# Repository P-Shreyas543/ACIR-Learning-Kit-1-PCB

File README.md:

# ACIR Learning Kits - Characterization & Experimentation Platform

**Decibels Lab Pvt Ltd**  
*Project Repository: [ACIR-Learning-Kit-1-PCB](https://github.com/P-Shreyas543/ACIR-Learning-Kit-1-PCB)*  
*Revision: v2.1 | Date: 2026-09-17*

---

## Overview

The **ACIR Learning Kits** are specialized, production-ready hardware characterization platforms designed for educational, research, and laboratory electrochemical impedance spectroscopy (EIS) and AC internal resistance (ACIR) testing of 18650 lithium-ion cells.

The repository contains two distinct learning kits:

### Learning Kit 1: Baseline Cell & Pack Topology Kit
1. **1S 1P Baseline Cell**: Single 18650 cell baseline ACIR characterization.
2. **1S 4P Parallel Pack**: Four-cell parallel module for current-sharing, contact resistance, and parallel cell mismatch studies.
3. **4S 1P Series String**: Four-cell series string for cumulative pack impedance and inter-cell busbar resistance.

### Learning Kit 2: Track Resistance & Interconnect Impedance Kit
1. **PCB Track Resistance Module**:
   - 3 calibrated test tracks with identical $6.0\text{ mm}$ width and varying lengths ($104.4\text{ mm}$, $58.0\text{ mm}$, $36.4\text{ mm}$).
   - Mirrored symmetrically on both copper layers (`F.Cu` and `B.Cu`).
   - Densely stitched with regular via matrices ($0.8\text{ mm}$ diameter, $0.4\text{ mm}$ drill).
   - Dedicated Kelvin test point probes: `P1` & `P2` (Track 1), `P3` & `P4` (Track 2), `P5` & `P6` (Track 3).
2. **4S 1P - (I) Module (Differential Cell ACIR Experiment)**:
   - 4 series cells (`BT2`, `BT3`, `BT4`, `BT5`) with uniform, ultra-low resistance interconnect buses ($8.0\text{ mm}$ 2-layer with dense via arrays).
   - Pack terminals: `B +ve` (BT2) and `B -ve` (BT5).
   - Students insert cells with *different* known ACIR values to observe that total pack ACIR is dominated by the sum of individual cell ACIRs when bus resistances are identical and negligible.
3. **4S 1P - (II) Module (Varying Interconnect Impedance Experiment)**:
   - 4 series cells (`BT6`, `BT7`, `BT8`, `BT9`) with deliberately *varying* interconnect track resistances:
     - **Link 1** (`BT6` $\leftrightarrow$ `BT7`): Ultra-wide $10.0\text{ mm}$ 2-layer bus with dense via matrix ($\approx 0.5\text{ m}\Omega$).
     - **Link 2** (`BT7` $\leftrightarrow$ `BT8`): Medium $3.0\text{ mm}$ single-layer trace ($\approx 3.0\text{ m}\Omega$).
     - **Link 3** (`BT8` $\leftrightarrow$ `BT9`): Narrow $0.8\text{ mm}$ single-layer trace ($\approx 10.0\text{ m}\Omega$).
   - Pack terminals: `B +ve` (BT6) and `B -ve` (BT9).
   - Students insert cells with *identical* ACIR values to demonstrate how interconnect trace impedance directly inflates total battery pack ACIR.

---

## Repository Structure

```
c:/Users/Shreyas/Documents/ACIR_PCB/
├── README.md                                  # Workspace Platform Documentation
├── .gitignore                                 # Git Ignore Configuration
├── ACIR-Learning-Kit-1-PCB/                   # Learning Kit 1 Project Directory
│   ├── ACIR-Learning-Kit-1-PCB.kicad_pro      # KiCad 10 Project File
│   ├── ACIR-Learning-Kit-1-PCB.kicad_pcb      # 2-Layer PCB Layout File
│   ├── ACIR-Learning-Kit-1-PCB.kicad_sch      # Complete Schematic Design
│   ├── ACIR-Learning-Kit-1-PCB.kicad_prl      # User Settings & Display Cache
│   ├── ACIR-Learning-Kit-1-PCB_BOM.csv        # Bill of Materials
│   ├── ACIR-Learning-Kit-1-PCB_LAYOUT.pdf     # Vector Layout Drawing
│   ├── ACIR-Learning-Kit-1-PCB_SCH.pdf        # Vector Schematic Drawing
│   ├── ACIR-Learning-Kit-1-PCB-drc.rpt        # DRC Verification Report (0 violations)
│   ├── ACIR-Learning-Kit-1-PCB-erc.rpt        # ERC Verification Report (0 errors)
│   ├── fp-lib-table                           # Footprint Library Table
│   ├── footprints.pretty/                     # Project Footprint Library
│   ├── gerbers/                               # RS-274X Gerbers & Drill Files
│   └── production/                            # JLCPCB Fabrication Deliverables
│       ├── ACIR-Learning-Kit-1-PCB_gerbers.zip# Complete Fabrication Archive
│       ├── ACIR-Learning-Kit-1-PCB_LAYOUT.pdf # Layout Drawing PDF
│       ├── ACIR-Learning-Kit-1-PCB_SCH.pdf    # Schematic Drawing PDF
│       ├── bom.csv                            # Component BOM
│       ├── positions.csv                      # Centroid Component Placement
│       └── netlist.ipc                        # IPC-D-356 Test Netlist
│
└── ACIR-Learning-Kit-2-PCB/                   # Learning Kit 2 Project Directory
    ├── ACIR-Learning-Kit-2-PCB.kicad_pro      # KiCad 10 Project File
    ├── ACIR-Learning-Kit-2-PCB.kicad_pcb      # 2-Layer PCB Layout File
    ├── ACIR-Learning-Kit-2-PCB.kicad_sch      # Complete Schematic Design
    ├── ACIR-Learning-Kit-2-PCB.kicad_prl      # User Settings & Display Cache
    ├── ACIR-Learning-Kit-2-PCB_BOM.csv        # Bill of Materials
    ├── ACIR-Learning-Kit-2-PCB_LAYOUT.pdf     # Vector Layout Drawing
    ├── ACIR-Learning-Kit-2-PCB_SCH.pdf        # Vector Schematic Drawing
    ├── ACIR-Learning-Kit-2-PCB-drc.rpt        # DRC Verification Report (0 violations)
    ├── ACIR-Learning-Kit-2-PCB-erc.rpt        # ERC Verification Report (0 errors)
    ├── kit2_render_top.png                    # Photorealistic 3D Top Render
    ├── kit2_render_bottom.png                 # Photorealistic 3D Bottom Render
    ├── fp-lib-table                           # Footprint Library Table
    ├── footprints.pretty/                     # Project Footprint Library
    ├── gerbers/                               # RS-274X Gerbers & Drill Files
    └── production/                            # JLCPCB Fabrication Deliverables
        ├── ACIR-Learning-Kit-2-PCB_gerbers.zip# Complete Fabrication Archive
        ├── ACIR-Learning-Kit-2-PCB_LAYOUT.pdf # Layout Drawing PDF
        ├── ACIR-Learning-Kit-2-PCB_SCH.pdf    # Schematic Drawing PDF
        ├── bom.csv                            # Component BOM
        ├── positions.csv                      # Centroid Component Placement
        └── netlist.ipc                        # IPC-D-356 Test Netlist
```

---

## PCB Specifications (Both Kits)

- **Dimensions**: $297.0\text{ mm} \times 210.0\text{ mm}$ (Standard A4 Landscape)
- **Layer Count**: 2 Layers ($1\text{ oz}$ / $35\,\mu\text{m}$ copper per layer)
- **Board Thickness**: $1.6\text{ mm}$ FR-4
- **Surface Finish**: HASL / ENIG compatible
- **Fabrication Compliance**: Verified 100% compliant with JLCPCB 2-layer fabrication capabilities:
  - **DRC**: **0 violations**, **0 unconnected pads**
  - **ERC**: **0 violations**, **0 errors**, **0 warnings**

---

## Design Team
- **Ashutosh Raj**
- **Shreyas P**
- **Suraj S D**

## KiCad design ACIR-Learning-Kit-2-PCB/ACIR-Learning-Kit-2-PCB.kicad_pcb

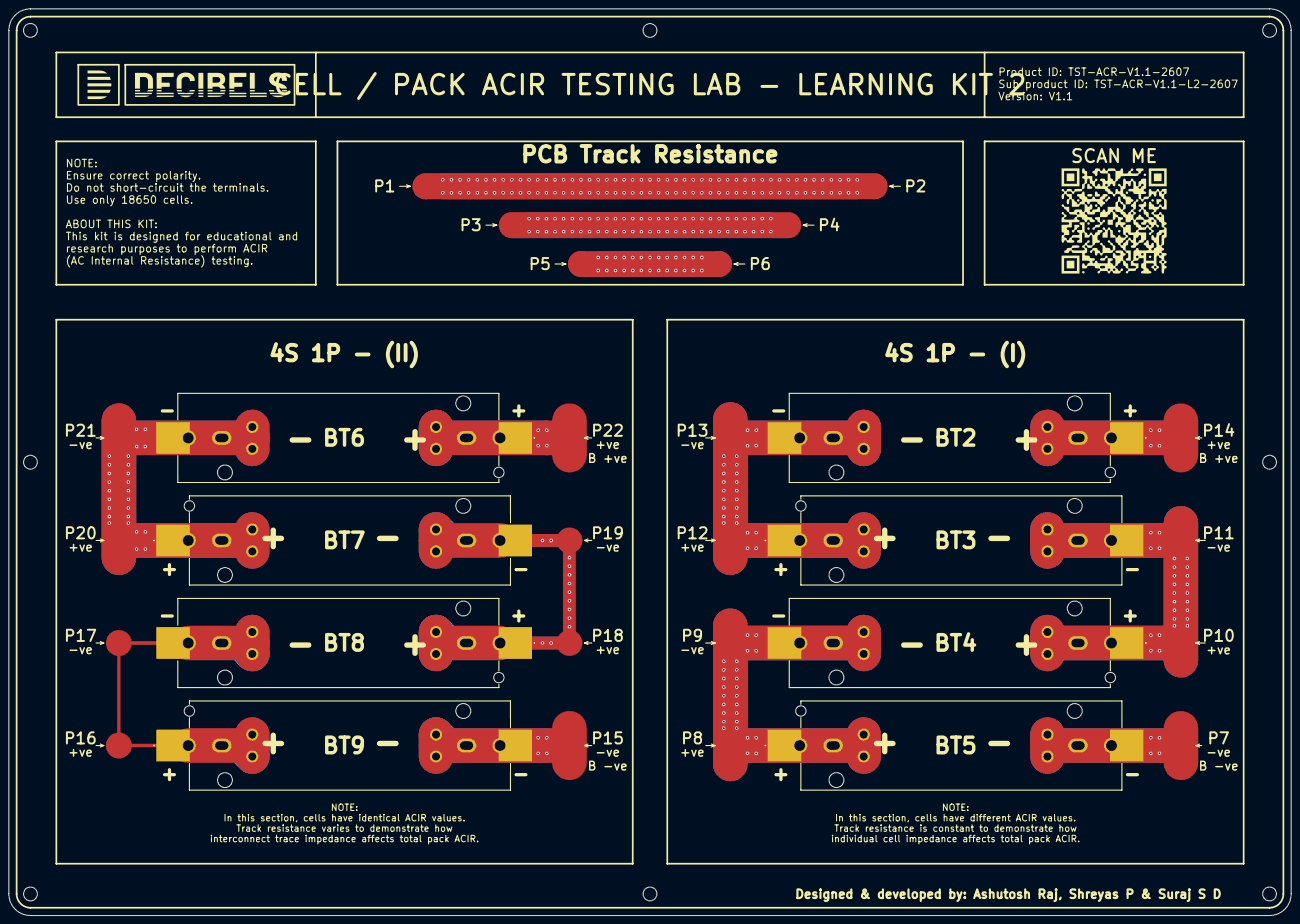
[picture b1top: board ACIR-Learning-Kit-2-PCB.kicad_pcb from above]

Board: 2 copper layers, 297.0 x 210.0 mm, 38 parts (0 on the bottom side), 13 nets.

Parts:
BT2, BT3, BT4, BT5, BT6, BT7, BT8, BT9: BH-18650-B5BA008; BH18650B1BA002
H1, H2, H3, H4, H5, H6, H7, H8: MountingHole_M3_Pad; MountingHole_3.2mm_M3
J3: 4S B +ve; TestPoint_Pad_D6.0mm
J4: 4S B -ve; TestPoint_Pad_D6.0mm
J7: 2S 1P +ve; TestPoint_Pad_D6.0mm
J8: 3S 1P +ve; TestPoint_Pad_D6.0mm
J9: 4S 1P +ve; TestPoint_Pad_D6.0mm
J10: 1S 1P +ve; TestPoint_Pad_D6.0mm
J11, J18: 1S 1P -ve; TestPoint_Pad_D6.0mm
J12: 1S 3P +ve; TestPoint_Pad_D6.0mm
J13: 1S 3P -ve; TestPoint_Pad_D6.0mm
J14: 1S 4P +ve; TestPoint_Pad_D6.0mm
J15: 1S 4P -ve; TestPoint_Pad_D6.0mm
J16: 1S 2P +ve; TestPoint_Pad_D6.0mm
J17: 1S 2P -ve; TestPoint_Pad_D6.0mm
J19: 2S 1P -ve; TestPoint_Pad_D6.0mm
J20: 3S 1P -ve; TestPoint_Pad_D6.0mm
P1, P4, P6: 1S 1P -ve; TestPoint_Pad_D6.0mm
P2, P3, P5: 1S 1P +ve; TestPoint_Pad_D6.0mm

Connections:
/4S_B+: BT2.1 (+), J3.1 (Pin_1_1)
/4S_B-: BT5.2 (-), J4.1 (Pin_1_1)
unnamed: BT2.2 (-), BT3.1 (+), J7.1 (Pin_1_1), J18.1 (Pin_1_1)
unnamed: BT3.2 (-), BT4.1 (+), J8.1 (Pin_1_1), J19.1 (Pin_1_1)
unnamed: BT4.2 (-), BT5.1 (+), J9.1 (Pin_1_1), J20.1 (Pin_1_1)
unnamed: BT6.1 (+), J10.1 (Pin_1_1)
unnamed: BT6.2 (-), BT7.1 (+), J11.1 (Pin_1_1), J13.1 (Pin_1_1)
unnamed: BT7.2 (-), BT8.1 (+), J12.1 (Pin_1_1), J14.1 (Pin_1_1)
unnamed: BT8.2 (-), BT9.1 (+), J15.1 (Pin_1_1), J17.1 (Pin_1_1)
unnamed: BT9.2 (-), J16.1 (Pin_1_1)
unnamed: P1.1 (Pin_1_1), P2.1 (Pin_1_1)
unnamed: P3.1 (Pin_1_1), P4.1 (Pin_1_1)
unnamed: P5.1 (Pin_1_1), P6.1 (Pin_1_1)
